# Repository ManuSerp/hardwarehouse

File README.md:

# Hardware projects
This repo contains Design sources, firmware, and fabrication exports for my electronics projects:

For detailed explanations and context, take a look at [my projects on Hackaday.io](https://hackaday.io/projects/hacker/1907261).

- `e-outlet/`: motorized outlet, enclosure, PCB, and ESP32 firmware. See the firmware README for setup and control commands.
- `irrigator/`: irrigation circuit designs and notes.
- `motordriver/`: motor driver circuits, documentation, and photographs.

Open KiCad projects with their project files and the included libraries. The outlet symbol library uses a project-relative path.

## Fabrication exports

The CNC `.nc` files and sliced `.3mf` files are machine-specific reference exports. Their original machine and slicer profiles have not been documented or validated for other equipment. Inspect units, origin, toolpaths, clearances, tooling, feeds, speeds, printer settings, and materials; regenerate for your own equipment before use.

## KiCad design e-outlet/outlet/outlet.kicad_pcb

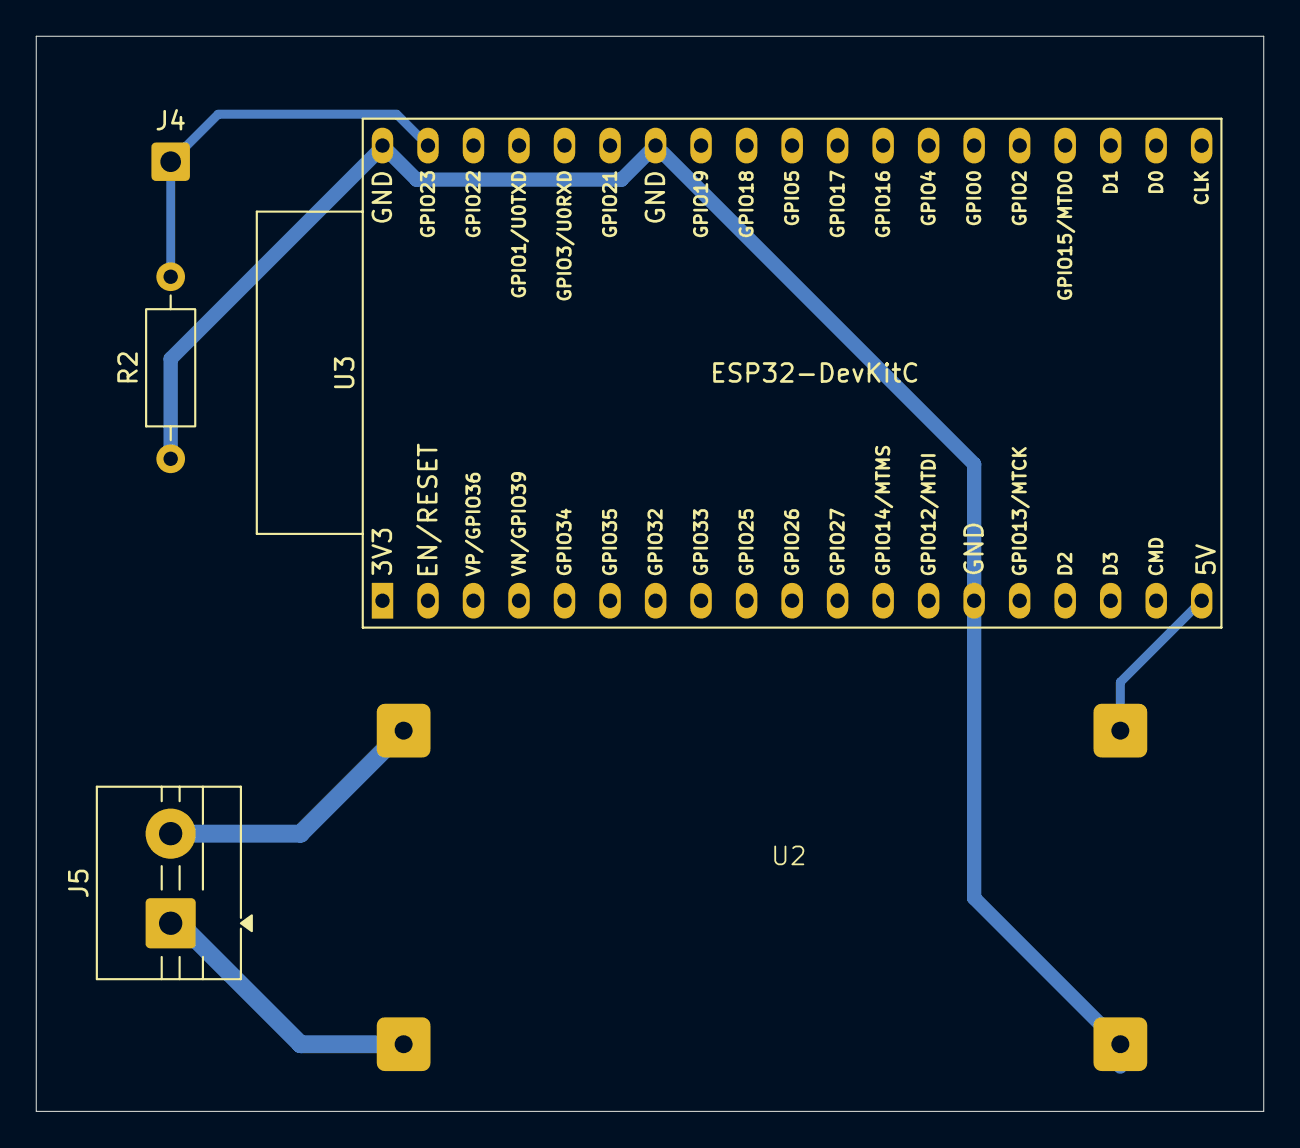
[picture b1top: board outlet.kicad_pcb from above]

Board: 2 copper layers, 68.5 x 60.0 mm, 5 parts (0 on the bottom side), 5 nets.

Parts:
J4: Conn_01x01_Pin; SolderWire-0.5sqmm_1x01_D0.9mm_OD2.1mm
J5: Conn_01x02_Pin; TerminalBlock_MaiXu_MX126-5.0-02P_1x02_P5.00mm
R2: R; R_Axial_DIN0207_L6.3mm_D2.5mm_P10.16mm_Horizontal
U2: LM2596_HW411_Carrier
U3: ESP32-DevKitC

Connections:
/buckplate/CMD: J4.1 (Pin_1_1), R2.2, U3.37 (GPIO23)
/buckplate/IN+: J5.2, U2.1 (IN+)
/buckplate/IN-: J5.1, U2.3 (IN-)
/buckplate/OUT+: U2.2 (OUT+), U3.19 (5V)
/buckplate/OUT-: R2.1, U2.4 (OUT-), U3.14 (GND), U3.32 (GND), U3.38 (GND)

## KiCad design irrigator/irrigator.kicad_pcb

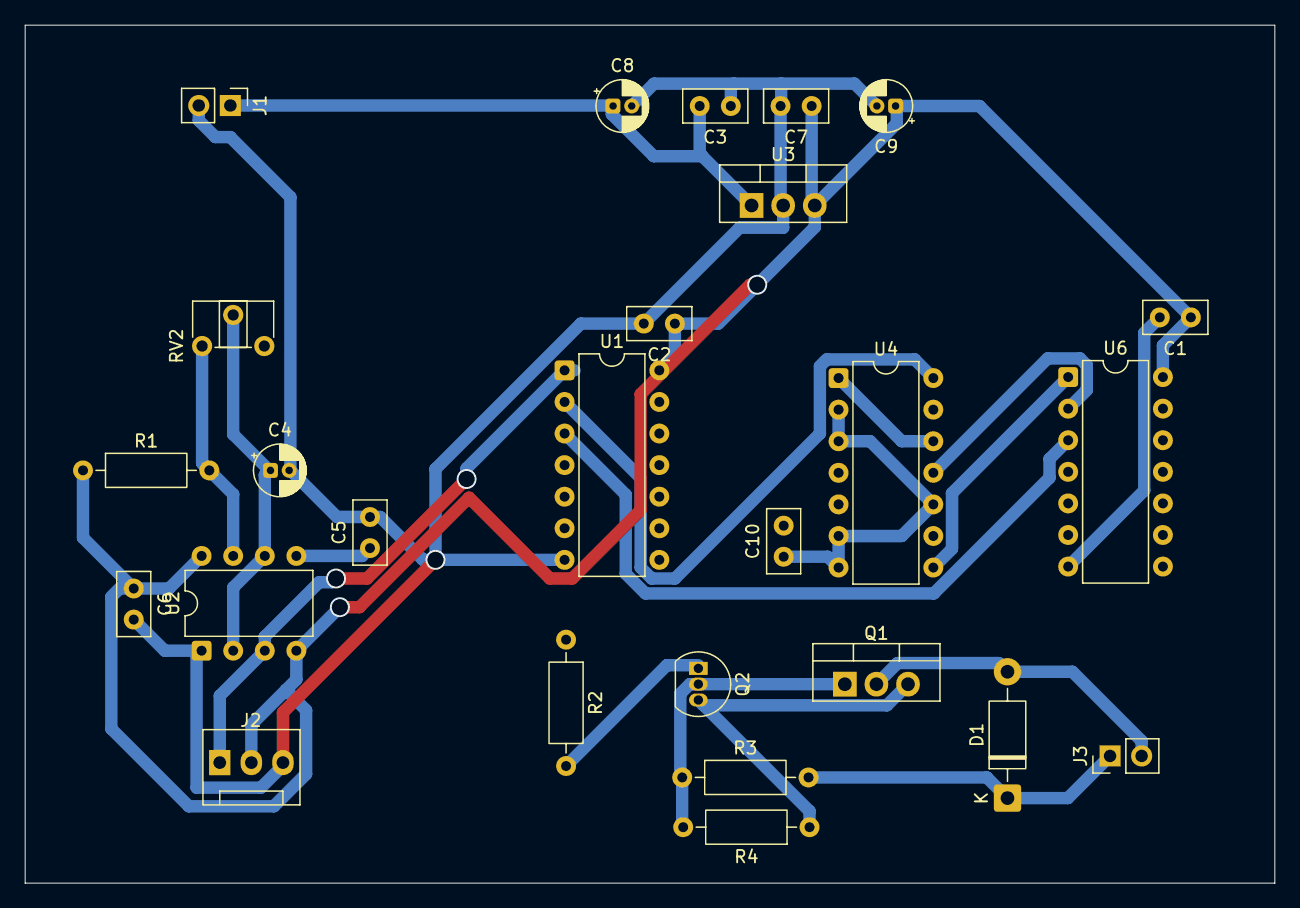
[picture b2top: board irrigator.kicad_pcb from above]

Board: 2 copper layers, 100.5 x 69.0 mm, 26 parts (0 on the bottom side), 16 nets.

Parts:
C1, C2, C3, C7, C10: 100nf; C_Disc_D5.0mm_W2.5mm_P2.50mm
C4: 1000uf; CP_Radial_D4.0mm_P1.50mm
C5: 10nf; C_Disc_D5.0mm_W2.5mm_P2.50mm
C6: 100nF; C_Disc_D5.0mm_W2.5mm_P2.50mm
C8, C9: 10uf; CP_Radial_D4.0mm_P1.50mm
D1: D; D_DO-41_SOD81_P10.16mm_Horizontal
J1, J3: Conn_01x02_Pin; PinHeader_1x02_P2.54mm_Vertical
J2: Conn_01x03_Socket; FanPinHeader_1x03_P2.54mm_Vertical
Q1: Q_NMOS_GDS; TO-220-3_Vertical
Q2: Q_NPN_BCE; TO-92_Inline
R1, R3: 10K; R_Axial_DIN0207_L6.3mm_D2.5mm_P10.16mm_Horizontal
R2: 4.7K; R_Axial_DIN0207_L6.3mm_D2.5mm_P10.16mm_Horizontal
R4: 100K; R_Axial_DIN0207_L6.3mm_D2.5mm_P10.16mm_Horizontal
RV2: 800kK; Potentiometer_ACP_CA6-H2,5_Horizontal
U1: 74HC14; DIP-14_W7.62mm
U2: ICM7555xP; DIP-8_W7.62mm
U3: L7805; TO-220-3_Vertical
U4: 74LS90; DIP-14_W7.62mm
U6: 74LS08; DIP-14_W7.62mm

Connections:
+12V: C3.2, C8.1, D1.1 (K), J1.1, J3.1, R3.2, U3.1 (IN)
/PUMP OUT: D1.2 (A), J3.2, Q1.2 (D)
/VCC +5V: C1.1, C2.1, C6.1, C7.1, C9.1, C10.2, J2.2, R1.1, U1.14 (VCC), U2.4 (~RST), U2.8 (VCC), U3.3 (OUT), U4.5 (VCC), U6.14 (VCC)
/timer/OUT: J2.1, U1.1, U2.3 (OUT)
GND: C1.2, C2.2, C3.1, C4.2, C5.2, C6.2, C7.2, C8.2, C9.2, C10.1, J1.2, J2.3, Q1.3 (S), Q2.3 (E), R4.1, U1.7 (GND), U2.1 (GND), U3.2 (GND), U4.2 (R0(1)), U4.3 (R0(2)), U4.6 (R9(1)), U4.7 (R9(2)), U4.10 (GND), U6.7 (GND)
unnamed: Q1.1 (G), Q2.2 (C), R3.1, R4.2
unnamed: Q2.1 (B), R2.2
unnamed: R2.1, U1.4
unnamed: U1.3, U6.3
unnamed: C5.1, U2.5 (CONT)
unnamed: R1.2, RV2.1, U2.7 (DISCH)
unnamed: C4.1, RV2.2, U2.2 (TRIG), U2.6 (THRES)
unnamed: U1.2, U4.14 (CP0)
unnamed: U4.1 (CP1..3), U4.12 (Q0)
unnamed: U4.8 (Q2), U6.1
unnamed: U4.11 (Q3), U6.2

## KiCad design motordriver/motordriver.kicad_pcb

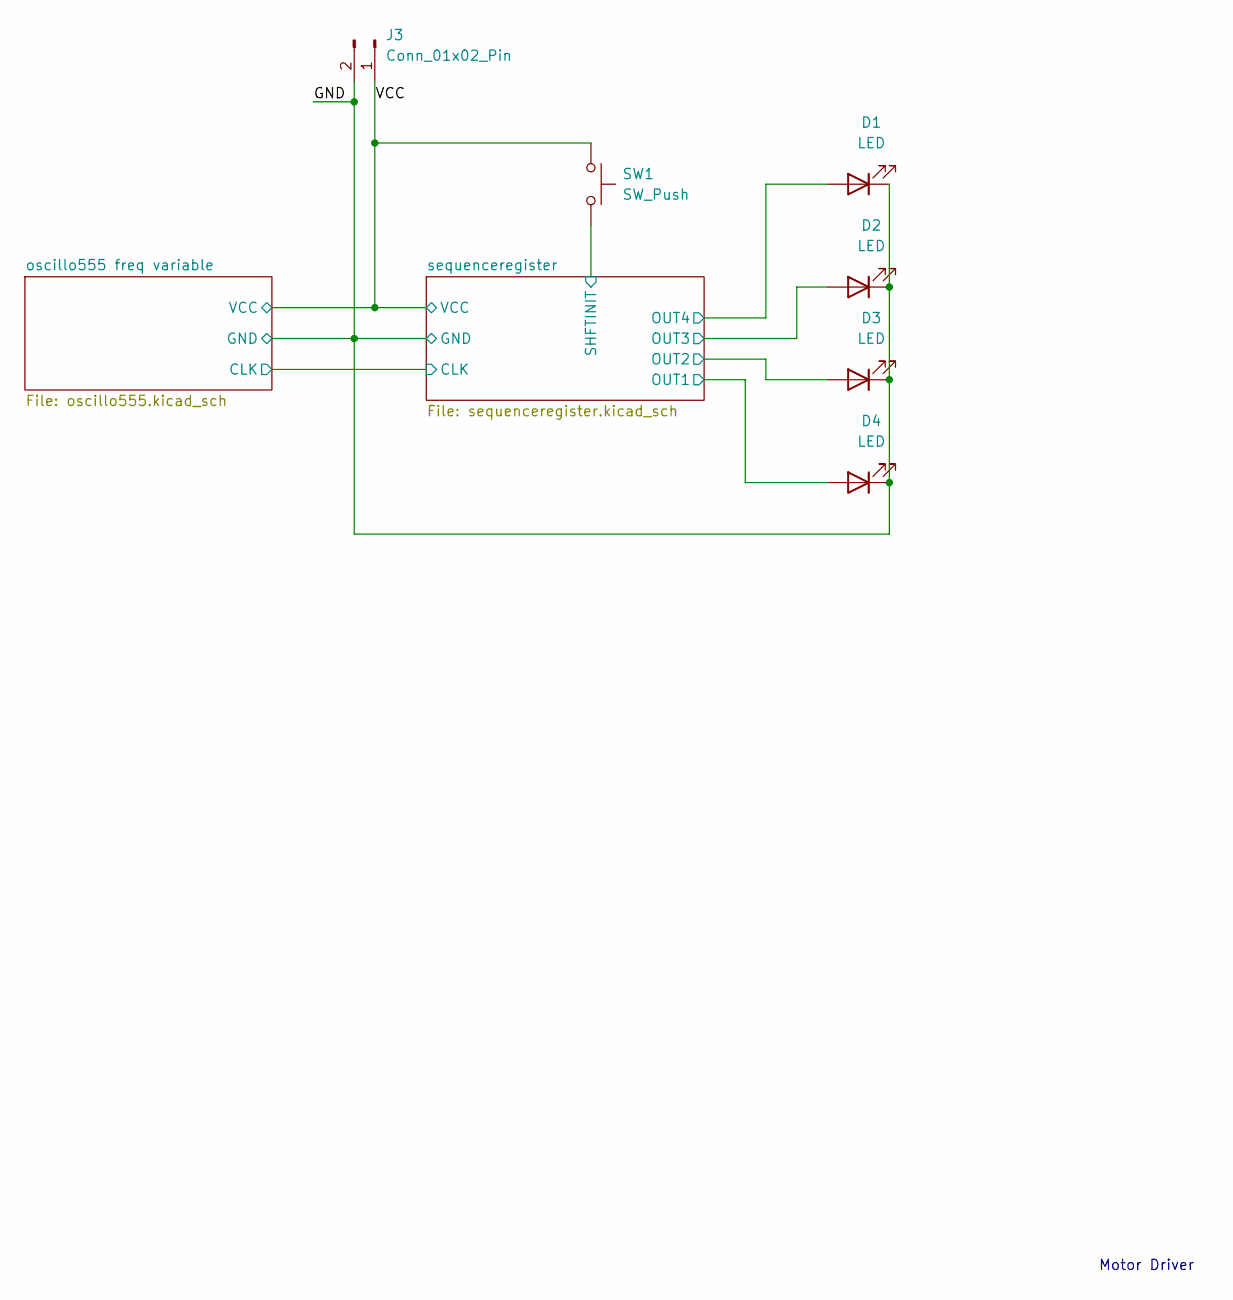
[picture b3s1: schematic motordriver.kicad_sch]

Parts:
D1, D2, D3, D4: LED; LED_D5.0mm
J3: Conn_01x02_Pin; JWT_A3963_1x02_P3.96mm_Vertical
SW1: SW_Push; SW_PUSH-12mm

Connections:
/GND: D1.1 (K), D2.1 (K), D3.1 (K), D4.1 (K), J3.2; also elsewhere on the board
/VCC: J3.1, SW1.1; also elsewhere on the board
/sequenceregister/OUT1: D4.2 (A); also elsewhere on the board
/sequenceregister/OUT2: D3.2 (A); also elsewhere on the board
/sequenceregister/OUT3: D2.2 (A); also elsewhere on the board
/sequenceregister/OUT4: D1.2 (A); also elsewhere on the board
/sequenceregister/SHFTINIT: SW1.2; also elsewhere on the board

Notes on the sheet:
Motor Driver

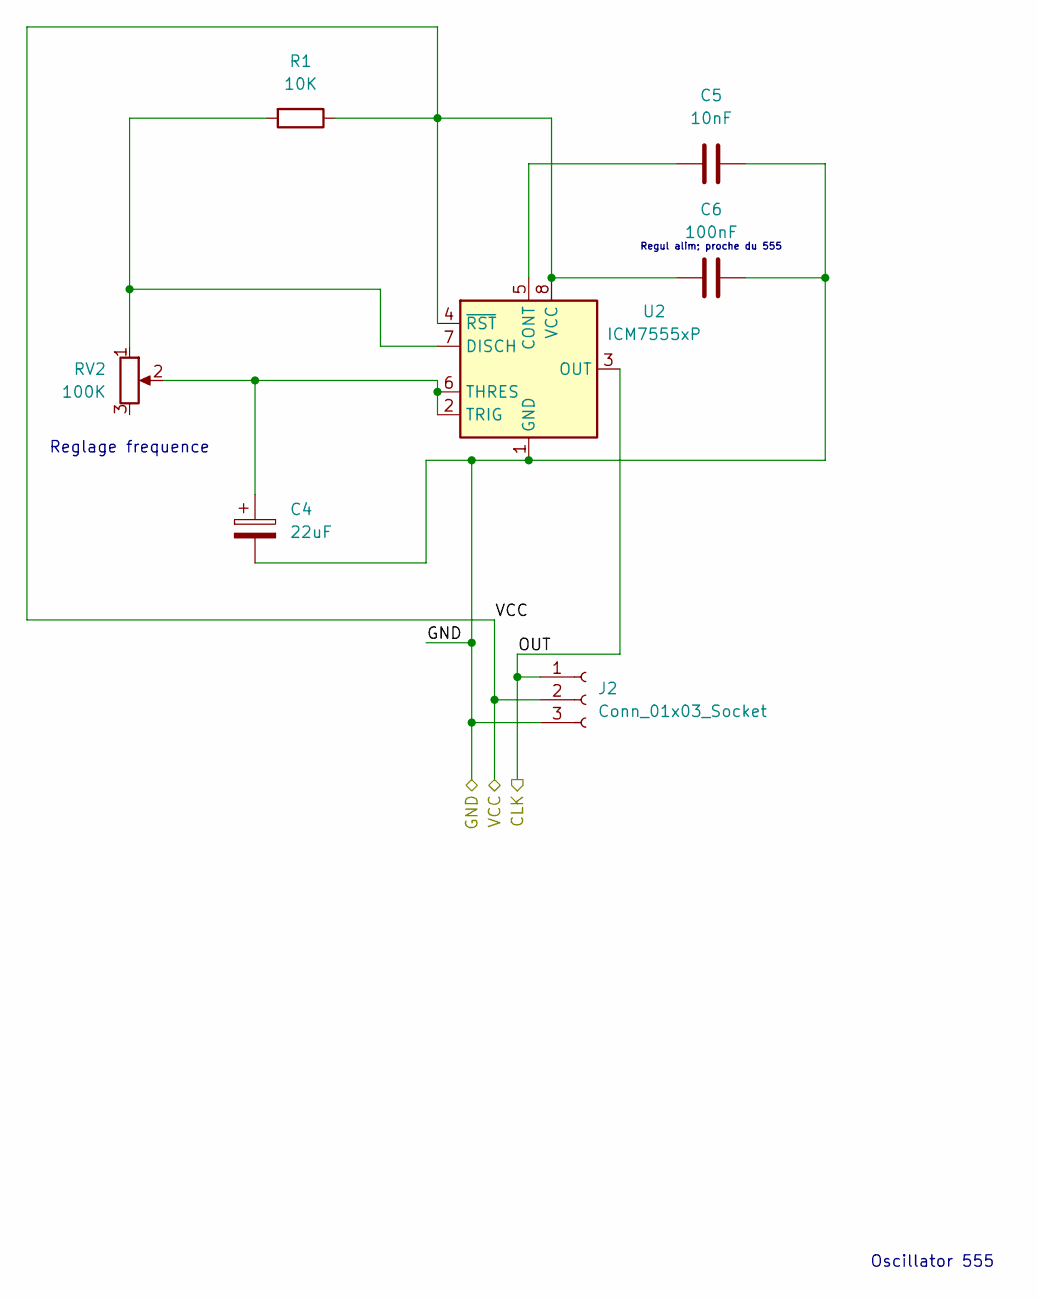
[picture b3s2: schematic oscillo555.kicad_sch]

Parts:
C4: 22uF; CP_Radial_D4.0mm_P1.50mm
C5: 10nF; C_Disc_D3.0mm_W1.6mm_P2.50mm
C6: 100nF; C_Disc_D3.0mm_W1.6mm_P2.50mm
J2: Conn_01x03_Socket; FanPinHeader_1x03_P2.54mm_Vertical
R1: 10K; R_Axial_DIN0204_L3.6mm_D1.6mm_P5.08mm_Horizontal
RV2: 100K; Potentiometer_ACP_CA6-H2,5_Horizontal
U2: ICM7555xP; DIP-8_W7.62mm

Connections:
/GND: C4.2, C5.2, C6.2, J2.3, U2.1 (GND); also elsewhere on the board
/VCC: C6.1, J2.2, R1.1, U2.4 (~RST), U2.8 (VCC); also elsewhere on the board
/oscillo555 freq variable/OUT: J2.1, U2.3 (OUT); also elsewhere on the board
unnamed: C5.1, U2.5 (CONT)
unnamed: R1.2, RV2.1, U2.7 (DISCH)
unnamed: C4.1, RV2.2, U2.2 (TRIG), U2.6 (THRES)

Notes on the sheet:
Oscillator 555
Regul alim; proche du 555
Reglage frequence

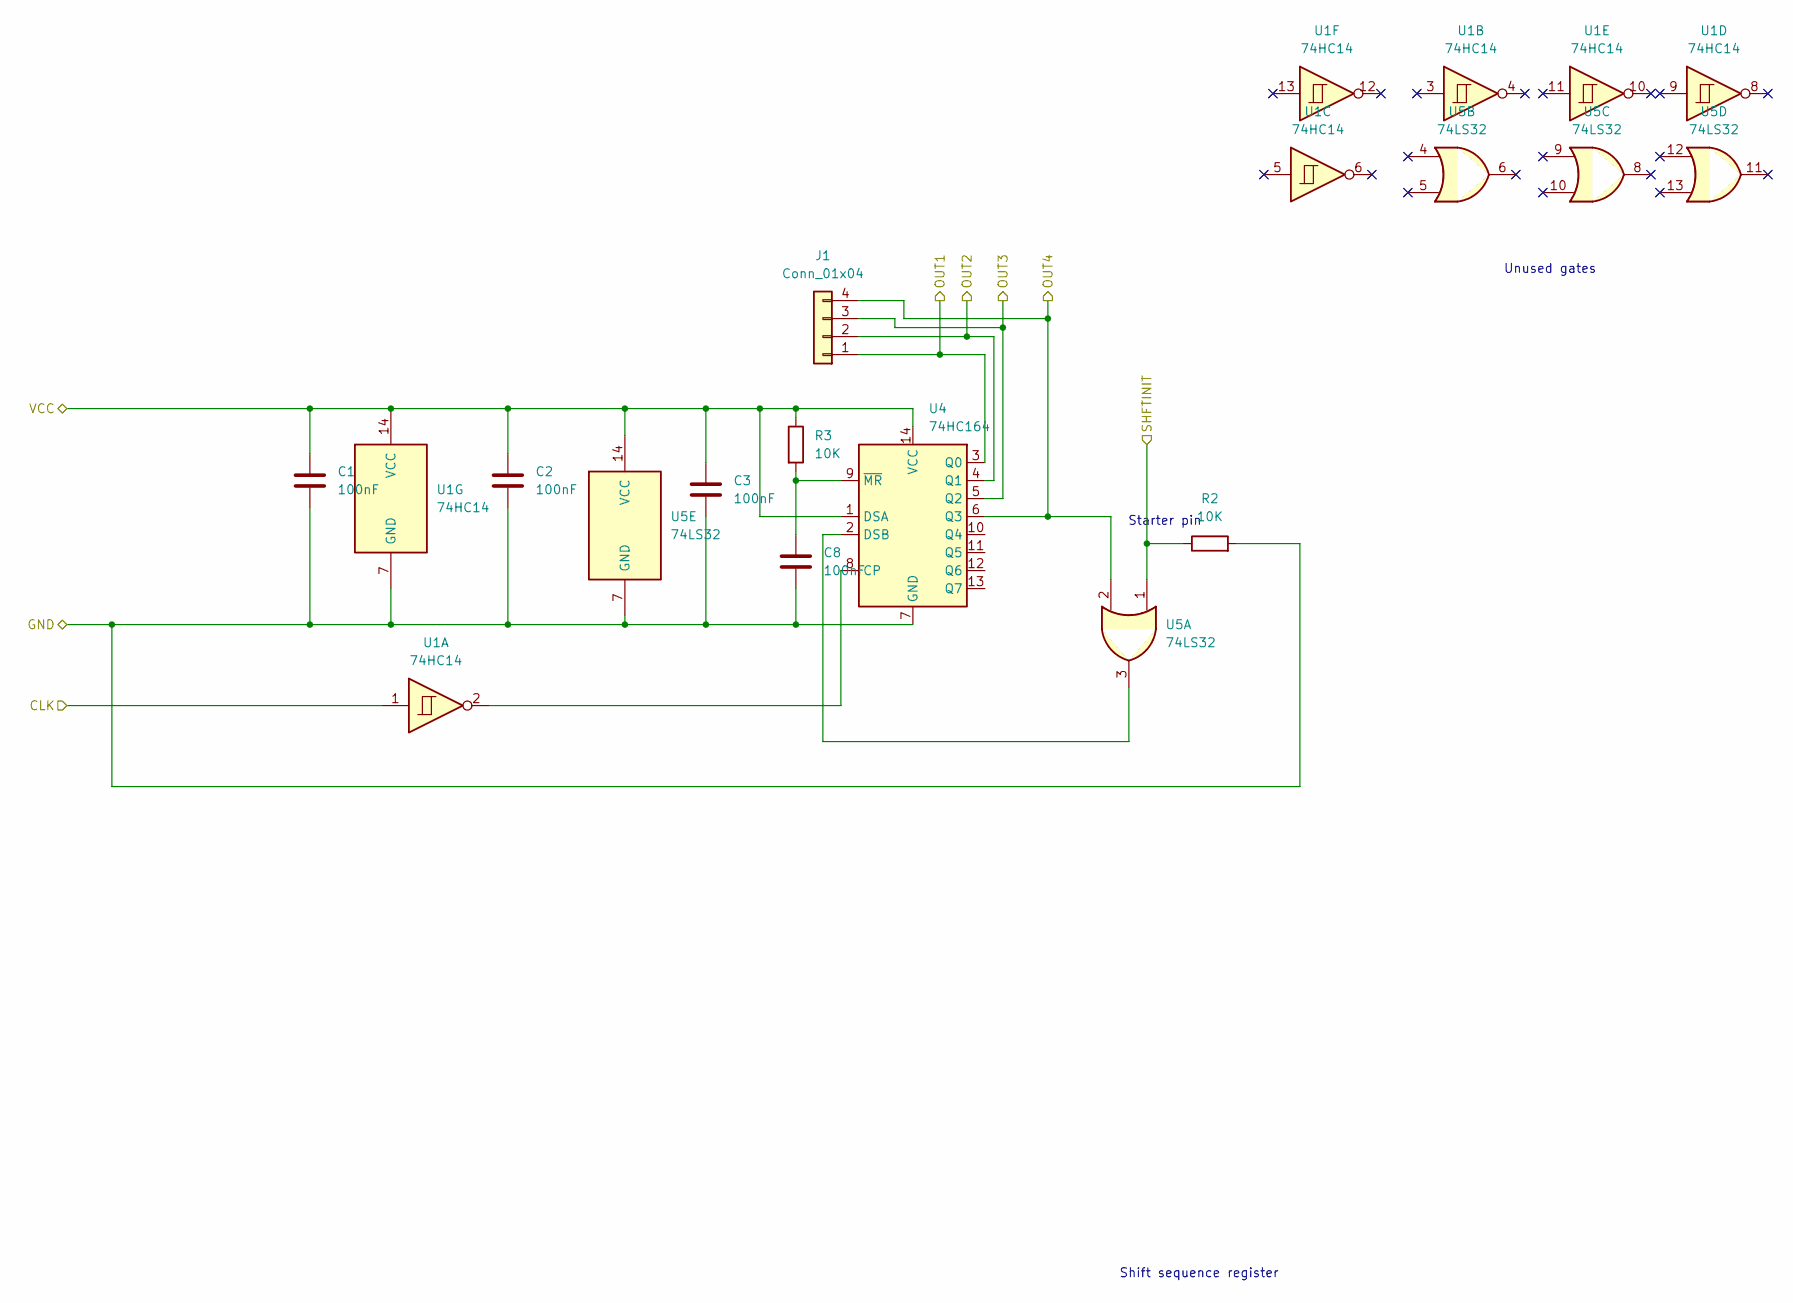
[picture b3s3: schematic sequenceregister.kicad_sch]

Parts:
C1, C2, C3, C8: 100nF; C_Disc_D3.0mm_W1.6mm_P2.50mm
J1: Conn_01x04; PinHeader_1x04_P2.54mm_Vertical
R2, R3: 10K; R_Axial_DIN0204_L3.6mm_D1.6mm_P5.08mm_Horizontal
U1: 74HC14; DIP-14_W7.62mm
U4: 74HC164; DIP-14_W7.62mm
U5: 74LS32; DIP-14_W7.62mm

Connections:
/GND: C1.2, C2.1, C3.1, C8.1, R2.2, U1.7 (GND), U4.7 (GND), U5.7 (GND); also elsewhere on the board
/VCC: C1.1, C2.2, C3.2, R3.1, U1.14 (VCC), U4.1 (DSA), U4.14 (VCC), U5.14 (VCC); also elsewhere on the board
/oscillo555 freq variable/OUT: U1.1; also elsewhere on the board
/sequenceregister/OUT1: J1.1, U4.3 (Q0); also elsewhere on the board
/sequenceregister/OUT2: J1.2, U4.4 (Q1); also elsewhere on the board
/sequenceregister/OUT3: J1.3, U4.5 (Q2); also elsewhere on the board
/sequenceregister/OUT4: J1.4, U4.6 (Q3), U5.2; also elsewhere on the board
/sequenceregister/SHFTINIT: R2.1, U5.1; also elsewhere on the board
unnamed: U1.2, U4.8 (CP)
unnamed: U4.2 (DSB), U5.3
unnamed: C8.2, R3.2, U4.9 (~MR)

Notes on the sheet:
Shift sequence register
Unused gates
Starter pin

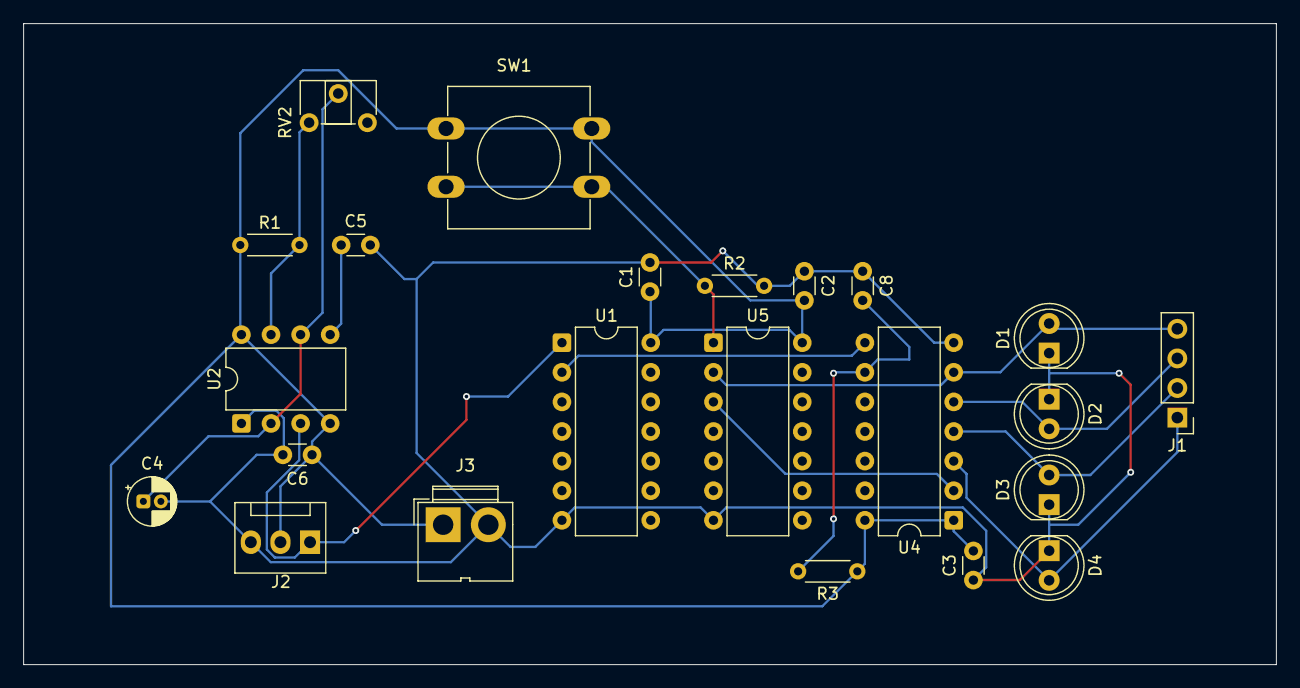
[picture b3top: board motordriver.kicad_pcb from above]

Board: 2 copper layers, 107.5 x 55.0 mm, 23 parts (0 on the bottom side), 14 nets.

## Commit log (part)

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2026-06-02 555 done
2026-06-03 Motordriver v1 (led insteqd of uln)
2026-06-03 final edit to current version that output a sequence
2026-06-06 finished routing
2026-06-09 oscillo assembled abd tested
2026-06-11 wip sodlering
2026-06-13 Finished
2026-06-16 start iriigator
2026-06-17 idee
2026-06-18 schema
2026-06-19 WIP scheme done now on PCB
